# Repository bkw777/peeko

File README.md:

# PEEKO

Alternate PCB for [gusmanb/logicanalyzer](https://github.com/gusmanb/logicanalyzer)

[PEEKO.bom.csv](PCB/out/PEEKO.bom.csv)

# BOM

[DigiKey](https://www.digikey.com/short/h755hpzf)  ([PEEKO.bom.csv](PCB/out/PEEKO.bom.csv))

<!--
Alternate parts for chain:  
[header molex 2-pin male r/a](https://www.digikey.com/en/products/detail/molex/1718574002/5116867)  
[cable molex 2-pin female-female 150mm](https://www.digikey.com/en/products/detail/molex/2177961021/14637993)  
TODO:  
* Zigzag pico pin holes  
  so pico can be installed removable with only male pins soldered to the pico  
  this elevates the pico by the same amount as the molex pin headers over the plain pin headers (2.54mm)  
* Version of enclosure with 2.54mm taller walls  
* Lid to close up the enclosure, with opening for heat sink for overclocked pico2
* Printable legend for the input pins
-->

# PROBES

Cable: https://www.digikey.com/en/products/detail/digilent-inc/310-064/5848557

Mini-grabbers: [terrible](https://www.amazon.com/dp/B07BCZSNGS), [good](https://amazon.com/dp/B09TPBS7YF/147-7256223-7410705), [expensive](https://www.amazon.com/dp/B00R3R7IVC)

# FIRMWARE

Download *-PICO.uf2 from https://github.com/gusmanb/logicanalyzer/releases  
Hold BOOTSEL button while connecting usb.  
Drag *-PICO.uf2 onto the RPI-RP2 drive.

PICO will reboot itself immediately and RPI-RP2 drive will disappear. PEEKO is ready to use.

# USAGE

For software, firmware, & directions, see [gusmanb/logicanalyzer/wiki](https://github.com/gusmanb/logicanalyzer/wiki)

# Other Versions

Brute-force diode-clamping version: [brute-clamp](brute-clamp.md)

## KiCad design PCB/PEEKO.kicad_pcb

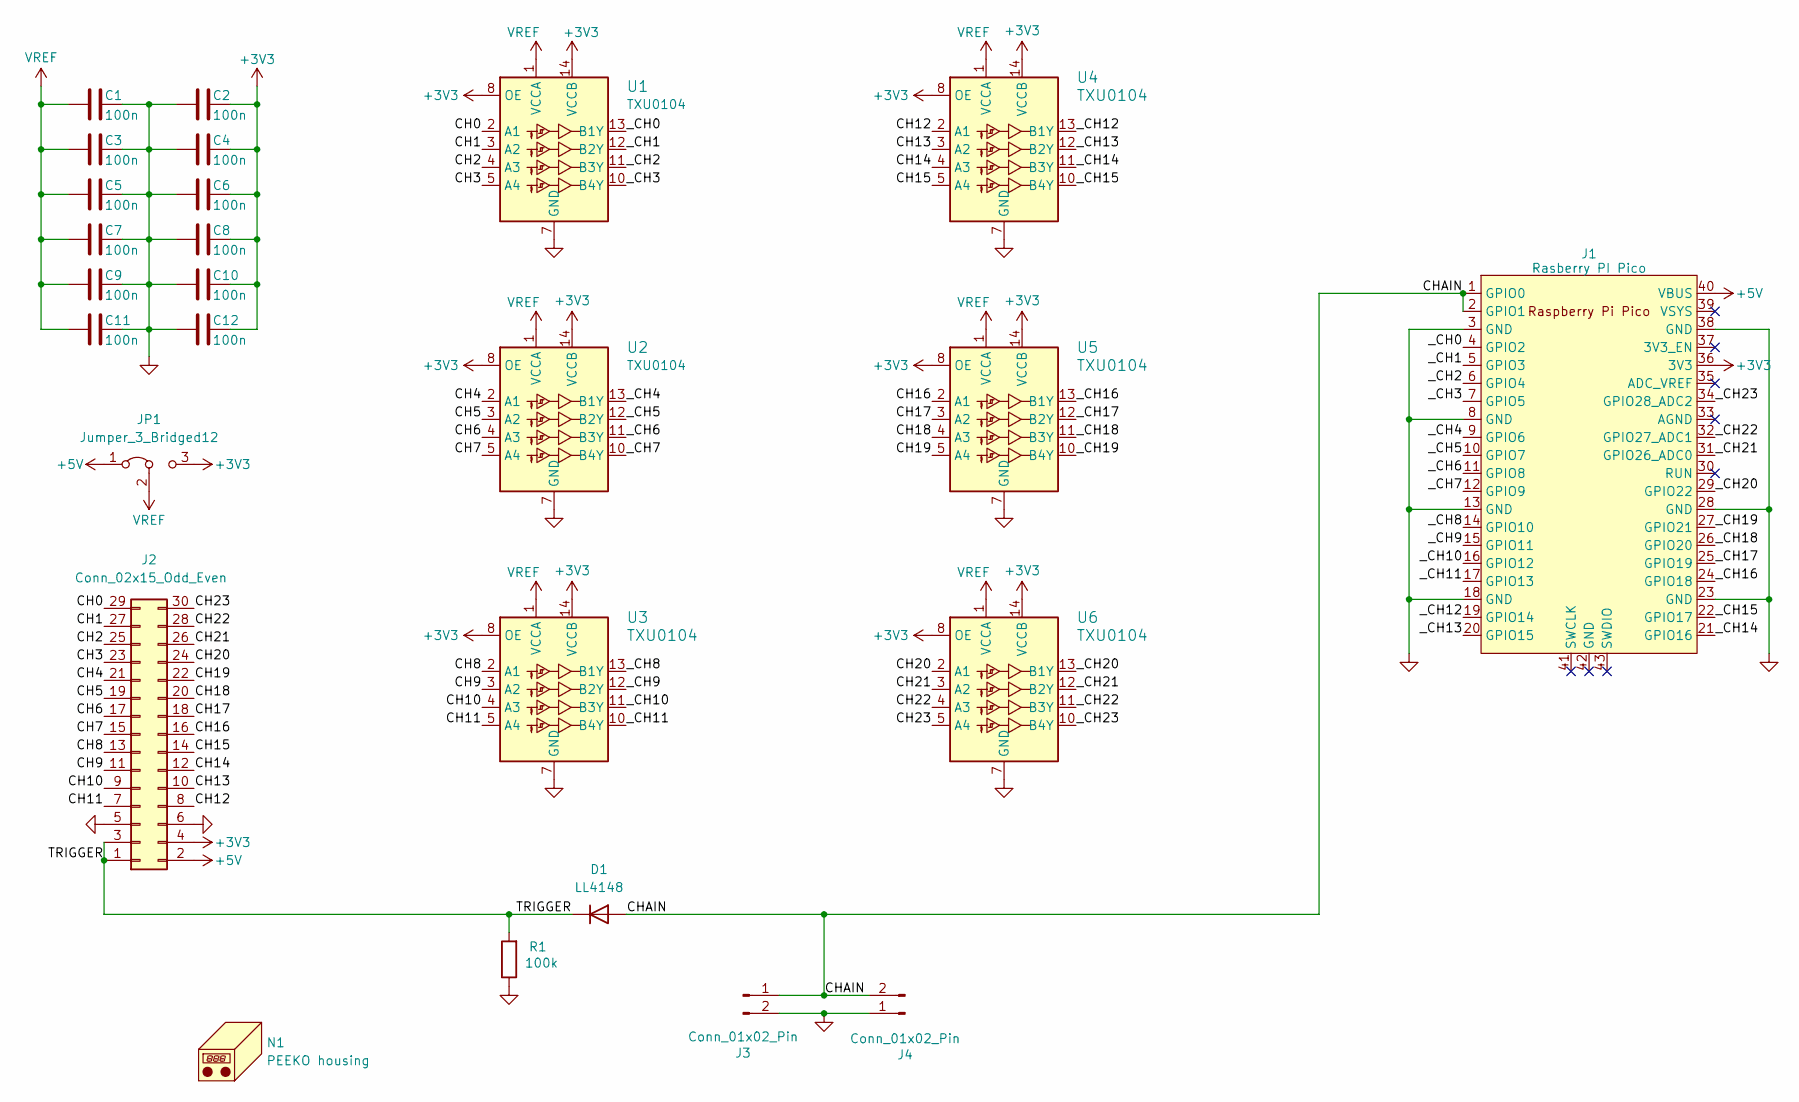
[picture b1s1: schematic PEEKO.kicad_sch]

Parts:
C1, C2, C3, C4, C5, C6, C7, C8, C9, C10, C11, C12: 100n; C_0805; MPN CC0805KRX7R9BB104
D1: LL4148; D_MiniMELF; MPN FDLL4148
J1: Rasberry PI Pico; dip-40-700-pi-pico-z; MPN SC0915
J2: Conn_02x15_Odd_Even; IDC_02x15_2.54_THT_male_pcb_edge; MPN SBH11-PBPC-D15-ST-BK
J3, J4: Conn_01x02_Pin; PinHeader_1x02_P2.54mm_Horizontal; MPN PH1RB-02-UA
JP1: Jumper_3_Bridged12; PinHeader_1x03_P2.54mm_Horizontal jumper 1-2; MPN PH1RB-03-UA
N1: PEEKO housing; PEEKO_housing
R1: 100k; R_0805; MPN RC0805FR-07100KL
U1, U2, U3, U4, U5, U6: TXU0104; TSSOP-14_4.4x5mm_P0.65mm; MPN TXU0104PW

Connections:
+3V3: C2.1, C4.1, C6.1, C8.1, C10.1, C12.1, J1.36 (3V3), J2.4, JP1.3 (B), U1.8 (OE), U1.14 (VCCB), U2.8 (OE), U2.14 (VCCB), U3.8 (OE), U3.14 (VCCB), U4.8 (OE), U4.14 (VCCB), U5.8 (OE), U5.14 (VCCB), U6.8 (OE), U6.14 (VCCB)
+5V: J1.40 (VBUS), J2.2, JP1.1 (A)
/CH0: J2.29, U1.2 (A1)
/CH1: J2.27, U1.3 (A2)
/CH2: J2.25, U1.4 (A3)
/CH3: J2.23, U1.5 (A4)
/CH4: J2.21, U2.2 (A1)
/CH5: J2.19, U2.3 (A2)
/CH6: J2.17, U2.4 (A3)
/CH7: J2.15, U2.5 (A4)
/CH8: J2.13, U3.2 (A1)
/CH9: J2.11, U3.3 (A2)
/CH10: J2.9, U3.4 (A3)
/CH11: J2.7, U3.5 (A4)
/CH12: J2.8, U4.2 (A1)
/CH13: J2.10, U4.3 (A2)
/CH14: J2.12, U4.4 (A3)
/CH15: J2.14, U4.5 (A4)
/CH16: J2.16, U5.2 (A1)
/CH17: J2.18, U5.3 (A2)
/CH18: J2.20, U5.4 (A3)
/CH19: J2.22, U5.5 (A4)
/CH20: J2.24, U6.2 (A1)
/CH21: J2.26, U6.3 (A2)
/CH22: J2.28, U6.4 (A3)
/CH23: J2.30, U6.5 (A4)
/CHAIN: D1.2 (A), J1.1 (GPIO0), J1.2 (GPIO1), J3.1, J4.2
/TRIGGER: D1.1 (K), J2.1, J2.3, R1.2
/_CH0: J1.4 (GPIO2), U1.13 (B1Y)
/_CH1: J1.5 (GPIO3), U1.12 (B2Y)
/_CH2: J1.6 (GPIO4), U1.11 (B3Y)
/_CH3: J1.7 (GPIO5), U1.10 (B4Y)
/_CH4: J1.9 (GPIO6), U2.13 (B1Y)
/_CH5: J1.10 (GPIO7), U2.12 (B2Y)
/_CH6: J1.11 (GPIO8), U2.11 (B3Y)
/_CH7: J1.12 (GPIO9), U2.10 (B4Y)
/_CH8: J1.14 (GPIO10), U3.13 (B1Y)
/_CH9: J1.15 (GPIO11), U3.12 (B2Y)
/_CH10: J1.16 (GPIO12), U3.11 (B3Y)
/_CH11: J1.17 (GPIO13), U3.10 (B4Y)
/_CH12: J1.19 (GPIO14), U4.13 (B1Y)
/_CH13: J1.20 (GPIO15), U4.12 (B2Y)
/_CH14: J1.21 (GPIO16), U4.11 (B3Y)
/_CH15: J1.22 (GPIO17), U4.10 (B4Y)
/_CH16: J1.24 (GPIO18), U5.13 (B1Y)
/_CH17: J1.25 (GPIO19), U5.12 (B2Y)
/_CH18: J1.26 (GPIO20), U5.11 (B3Y)
/_CH19: J1.27 (GPIO21), U5.10 (B4Y)
/_CH20: J1.29 (GPIO22), U6.13 (B1Y)
/_CH21: J1.31 (GPIO26_ADC0), U6.12 (B2Y)
/_CH22: J1.32 (GPIO27_ADC1), U6.11 (B3Y)
/_CH23: J1.34 (GPIO28_ADC2), U6.10 (B4Y)
GND: C1.1, C2.2, C3.1, C4.2, C5.1, C6.2, C7.1, C8.2, C9.1, C10.2, C11.1, C12.2, J1.3 (GND), J1.8 (GND), J1.13 (GND), J1.18 (GND), J1.23 (GND), J1.28 (GND), J1.38 (GND), J2.5, J2.6, J3.2, J4.1, R1.1, U1.7 (GND), U2.7 (GND), U3.7 (GND), U4.7 (GND), U5.7 (GND), U6.7 (GND)
VREF: C1.2, C3.2, C5.2, C7.2, C9.2, C11.2, JP1.2 (C), U1.1 (VCCA), U2.1 (VCCA), U3.1 (VCCA), U4.1 (VCCA), U5.1 (VCCA), U6.1 (VCCA)

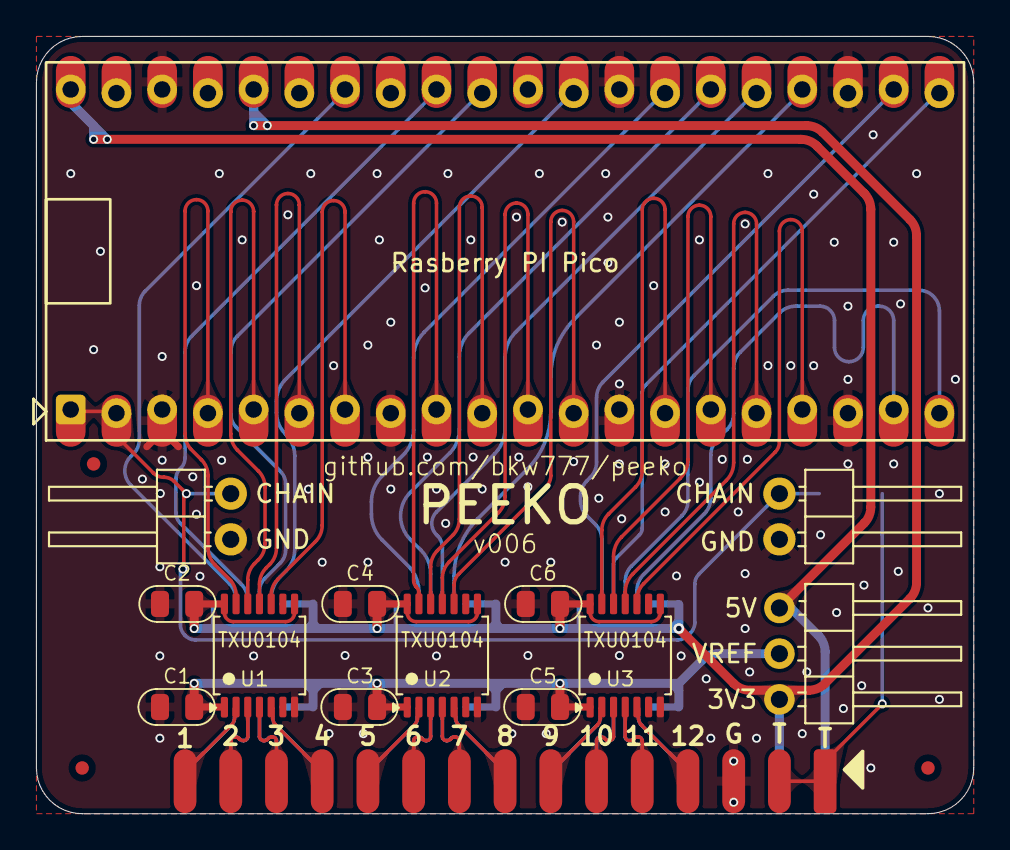
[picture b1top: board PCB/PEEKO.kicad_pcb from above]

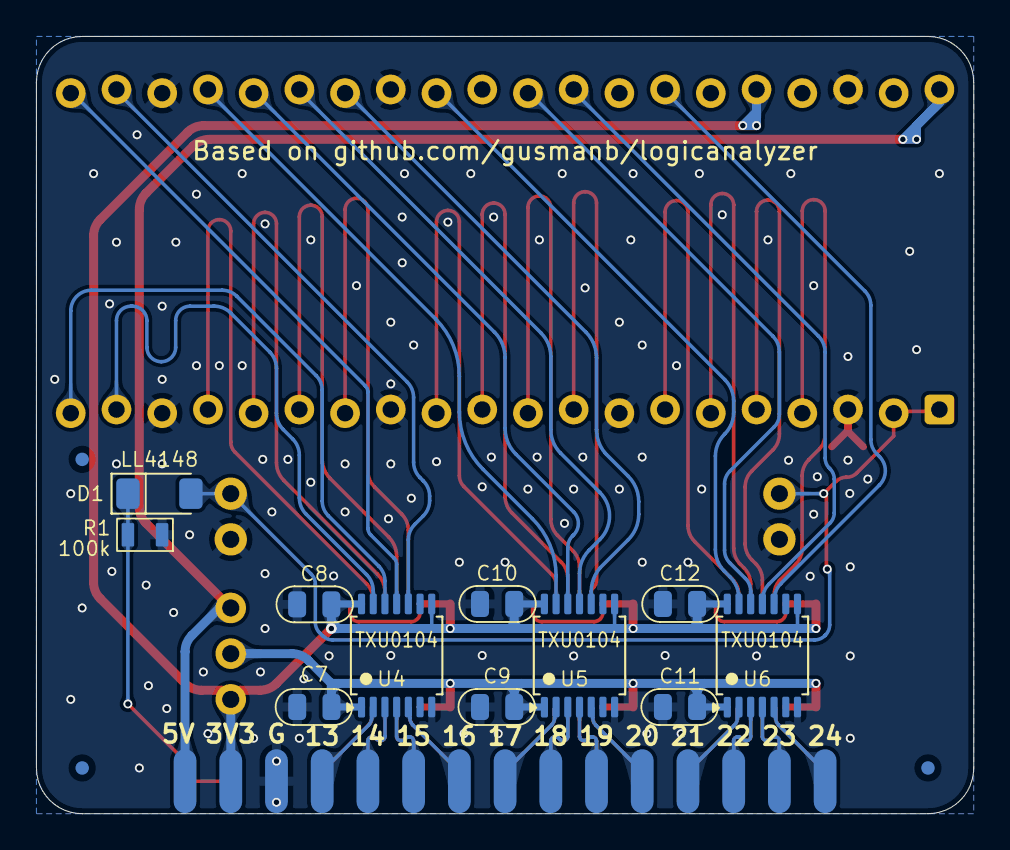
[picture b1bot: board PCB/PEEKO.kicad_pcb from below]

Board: 2 copper layers, 52.1 x 43.2 mm, 26 parts (11 on the bottom side), 54 nets.

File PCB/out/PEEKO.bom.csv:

"Reference","Value","Datasheet","Footprint","Qty","DNP","MPN","Description"
"C1,C2,C3,C4,C5,C6,C7,C8,C9,C10,C11,C12","100n","datasheets/UPY-GPHC_X7R_6.3V-to-250V_24.pdf","000_LOCAL:C_0805","12","","CC0805KRX7R9BB104","CAP CER 0.1UF 50V X7R 0805"
"D1","LL4148","datasheets/ll4148.pdf","000_LOCAL:D_MiniMELF","1","","FDLL4148","50V 1A General Purpose Rectifier Diode"
"J1","Rasberry PI Pico","datasheets/rpi-pico.pdf","000_LOCAL:dip-40-700-pi-pico","1","","SC0915","RASPBERRY PI PICO RP2040"
"J2","Conn_02x15_Odd_Even","datasheets/SBH11.pdf","000_LOCAL:IDC_02x15_2.54_THT_male_pcb_edge","1","","SBH11-PBPC-D15-ST-BK","CONN HEADER VERT 30POS 2.54MM"
"J3,J4","Conn_01x02_Pin","~","000_LOCAL:PinHeader_1x02_P2.54mm_Horizontal","2","","PH1RB-02-UA","CONN HEADER R/A 2POS 2.54MM"
"R1","100k","datasheets/PYu-RC_Group_51_RoHS_L_12.pdf","000_LOCAL:R_0805","1","","RC0805FR-07100KL","RES 100K OHM 1% 1/8W 0805"
"U1,U2,U3,U4,U5,U6","TXU0104","datasheets/txu0104.pdf","000_LOCAL:TSSOP-14_4.4x5mm_P0.65mm","6","","TXU0104PW","4-Bit Unidirectional Voltage-Level Translator, Schmitt trigger input, tri-state output, 1.1v to 5.5v, vTSSOP-14"

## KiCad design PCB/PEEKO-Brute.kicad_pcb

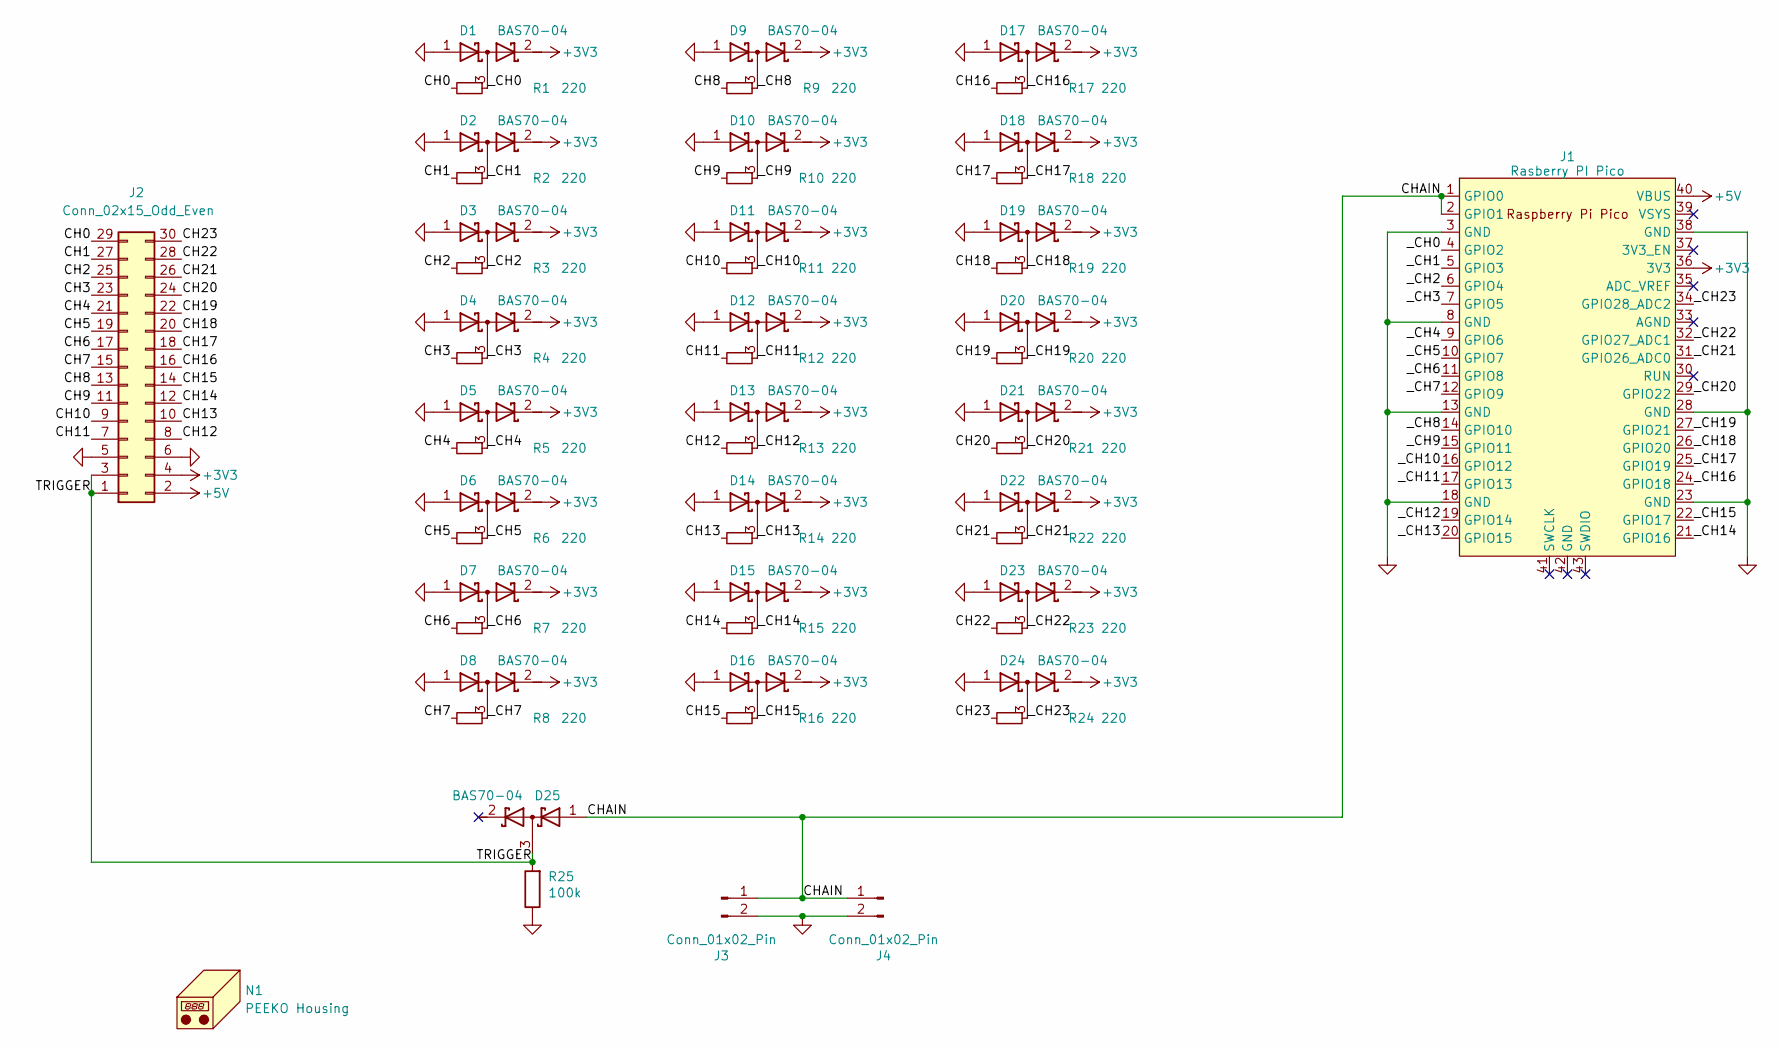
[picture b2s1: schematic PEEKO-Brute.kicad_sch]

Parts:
D1, D2, D3, D4, D5, D6, D7, D8, D9, D10, D11, D12, D13, D14, D15, D16, D17, D18, D19, D20, D21, D22, D23, D24, D25: BAS70-04; SC-59
J1: Rasberry PI Pico; dip-40-700-pi-pico; MPN SC0915
J2: Conn_02x15_Odd_Even; IDC_02x15_2.54_THT_male_pcb_edge; MPN SBH11-PBPC-D15-ST-BK
J3, J4: Conn_01x02_Pin; PinHeader_1x02_P2.54mm_Horizontal; MPN PH1RB-02-UA
N1: PEEKO Housing; PEEKO_housing
R1, R2, R3, R4, R5, R6, R7, R8, R9, R10, R11, R12, R13, R14, R15, R16, R17, R18, R19, R20, R21, R22, R23, R24: 220; R_0805; MPN CRGCQ0805F220R
R25: 100k; R_0805; MPN RC0805FR-07100KL

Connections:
+3V3: D1.2 (K), D2.2 (K), D3.2 (K), D4.2 (K), D5.2 (K), D6.2 (K), D7.2 (K), D8.2 (K), D9.2 (K), D10.2 (K), D11.2 (K), D12.2 (K), D13.2 (K), D14.2 (K), D15.2 (K), D16.2 (K), D17.2 (K), D18.2 (K), D19.2 (K), D20.2 (K), D21.2 (K), D22.2 (K), D23.2 (K), D24.2 (K), J1.36 (3V3), J2.4
+5V: J1.40 (VBUS), J2.2
/CH0: J2.29, R1.2
/CH1: J2.27, R2.2
/CH2: J2.25, R3.2
/CH3: J2.23, R4.2
/CH4: J2.21, R5.2
/CH5: J2.19, R6.2
/CH6: J2.17, R7.2
/CH7: J2.15, R8.2
/CH8: J2.13, R9.2
/CH9: J2.11, R10.2
/CH10: J2.9, R11.2
/CH11: J2.7, R12.2
/CH12: J2.8, R13.2
/CH13: J2.10, R14.2
/CH14: J2.12, R15.2
/CH15: J2.14, R16.2
/CH16: J2.16, R17.2
/CH17: J2.18, R18.2
/CH18: J2.20, R19.2
/CH19: J2.22, R20.2
/CH20: J2.24, R21.2
/CH21: J2.26, R22.2
/CH22: J2.28, R23.2
/CH23: J2.30, R24.2
/CHAIN: D25.1 (A), J1.1 (GPIO0), J1.2 (GPIO1), J3.1, J4.1
/TRIGGER: D25.3 (common), J2.1, J2.3, R25.2
/_CH0: D1.3 (common), J1.4 (GPIO2), R1.1
/_CH1: D2.3 (common), J1.5 (GPIO3), R2.1
/_CH2: D3.3 (common), J1.6 (GPIO4), R3.1
/_CH3: D4.3 (common), J1.7 (GPIO5), R4.1
/_CH4: D5.3 (common), J1.9 (GPIO6), R5.1
/_CH5: D6.3 (common), J1.10 (GPIO7), R6.1
/_CH6: D7.3 (common), J1.11 (GPIO8), R7.1
/_CH7: D8.3 (common), J1.12 (GPIO9), R8.1
/_CH8: D9.3 (common), J1.14 (GPIO10), R9.1
/_CH9: D10.3 (common), J1.15 (GPIO11), R10.1
/_CH10: D11.3 (common), J1.16 (GPIO12), R11.1
/_CH11: D12.3 (common), J1.17 (GPIO13), R12.1
/_CH12: D13.3 (common), J1.19 (GPIO14), R13.1
/_CH13: D14.3 (common), J1.20 (GPIO15), R14.1
/_CH14: D15.3 (common), J1.21 (GPIO16), R15.1
/_CH15: D16.3 (common), J1.22 (GPIO17), R16.1
/_CH16: D17.3 (common), J1.24 (GPIO18), R17.1
/_CH17: D18.3 (common), J1.25 (GPIO19), R18.1
/_CH18: D19.3 (common), J1.26 (GPIO20), R19.1
/_CH19: D20.3 (common), J1.27 (GPIO21), R20.1
/_CH20: D21.3 (common), J1.29 (GPIO22), R21.1
/_CH21: D22.3 (common), J1.31 (GPIO26_ADC0), R22.1
/_CH22: D23.3 (common), J1.32 (GPIO27_ADC1), R23.1
/_CH23: D24.3 (common), J1.34 (GPIO28_ADC2), R24.1
GND: D1.1 (A), D2.1 (A), D3.1 (A), D4.1 (A), D5.1 (A), D6.1 (A), D7.1 (A), D8.1 (A), D9.1 (A), D10.1 (A), D11.1 (A), D12.1 (A), D13.1 (A), D14.1 (A), D15.1 (A), D16.1 (A), D17.1 (A), D18.1 (A), D19.1 (A), D20.1 (A), D21.1 (A), D22.1 (A), D23.1 (A), D24.1 (A), J1.3 (GND), J1.8 (GND), J1.13 (GND), J1.18 (GND), J1.23 (GND), J1.28 (GND), J1.38 (GND), J2.5, J2.6, J3.2, J4.2, R25.1

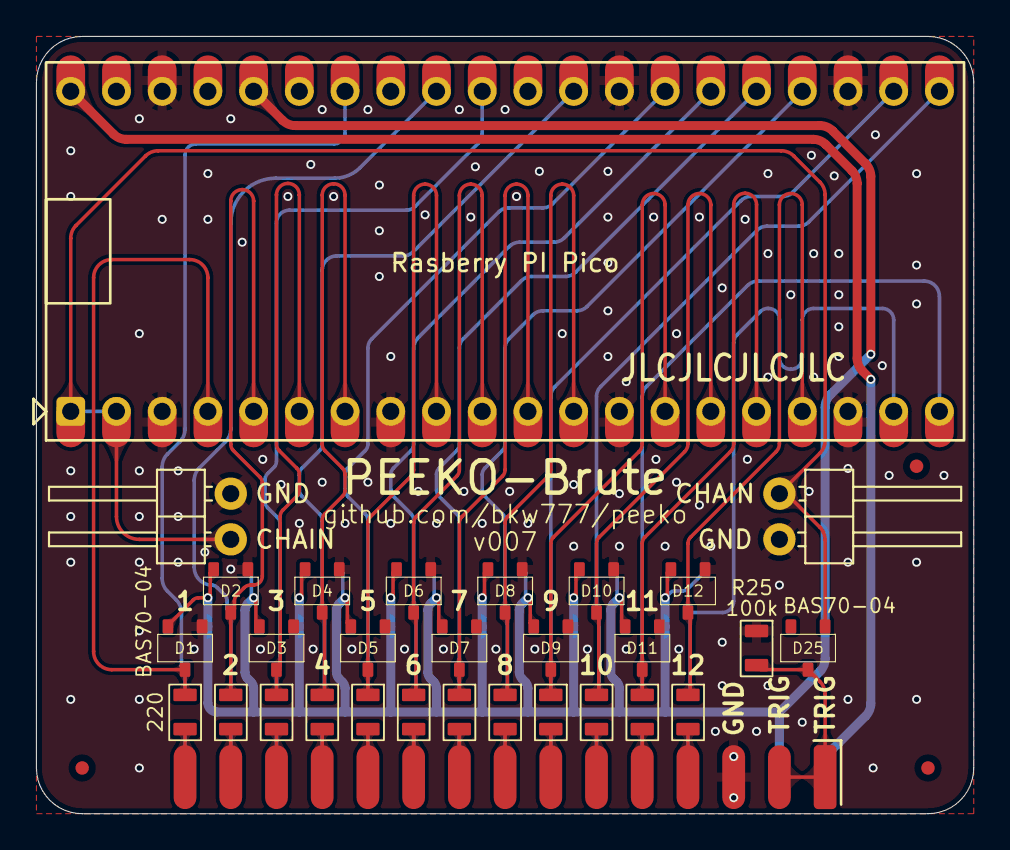
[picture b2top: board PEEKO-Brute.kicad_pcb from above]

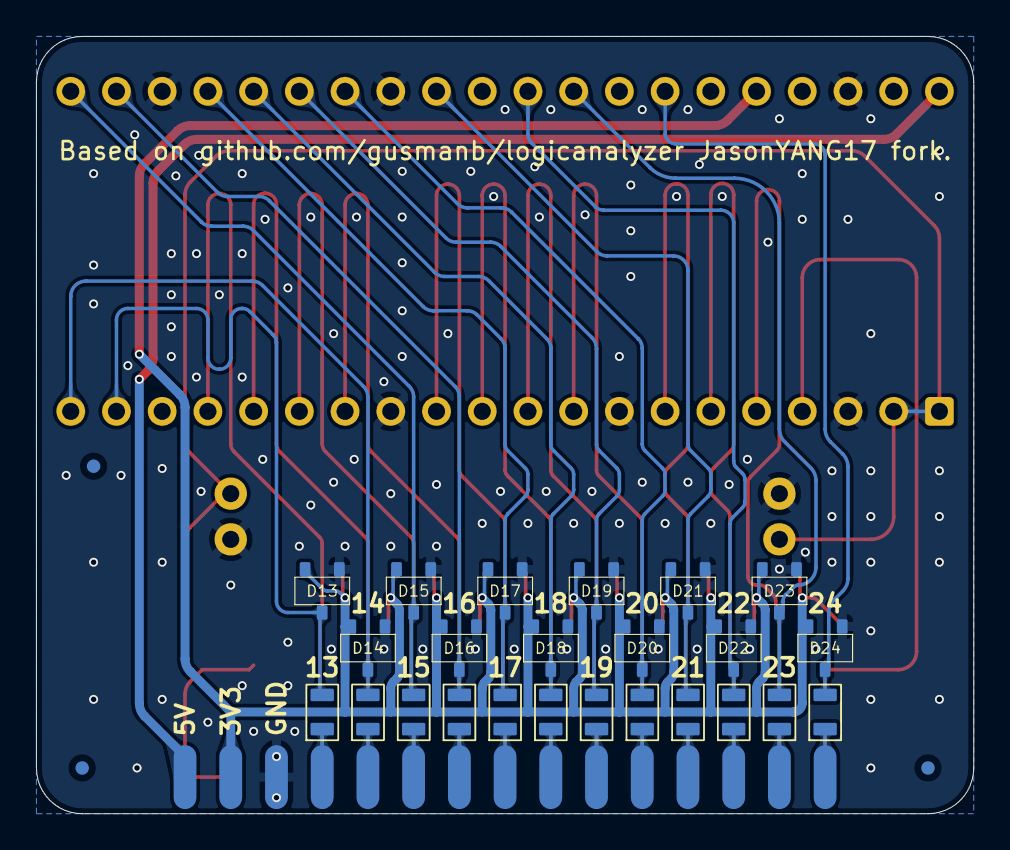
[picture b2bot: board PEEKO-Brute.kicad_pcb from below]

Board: 2 copper layers, 52.1 x 43.2 mm, 55 parts (24 on the bottom side), 53 nets.

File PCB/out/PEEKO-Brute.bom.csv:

"Reference","Value","Datasheet","Footprint","Qty","DNP","MPN"
"D1,D2,D3,D4,D5,D6,D7,D8,D9,D10,D11,D12,D13,D14,D15,D16,D17,D18,D19,D20,D21,D22,D23,D24,D25","BAS70-04","datasheets/INFNS30154-1.pdf","000_LOCAL:SC-59","25","","BAS70-04"
"J1","Rasberry PI Pico","datasheets/rpi-pico.pdf","000_LOCAL:dip-40-700-pi-pico","1","","SC0915"
"J2","Conn_02x15_Odd_Even","datasheets/SBH11.pdf","000_LOCAL:IDC_02x15_2.54_THT_male_pcb_edge","1","","SBH11-PBPC-D15-ST-BK"
"J3,J4","Conn_01x02_Pin","~","000_LOCAL:PinHeader_1x02_P2.54mm_Horizontal","2","","PH1RB-02-UA"
"R1,R2,R3,R4,R5,R6,R7,R8,R9,R10,R11,R12,R13,R14,R15,R16,R17,R18,R19,R20,R21,R22,R23,R24","220","datasheets/TE-1-2176341-7.pdf","000_LOCAL:R_0805","24","","CRGCQ0805F220R"
"R25","100k","datasheets/PYu-RC_Group_51_RoHS_L_12.pdf","000_LOCAL:R_0805","1","","RC0805FR-07100KL"

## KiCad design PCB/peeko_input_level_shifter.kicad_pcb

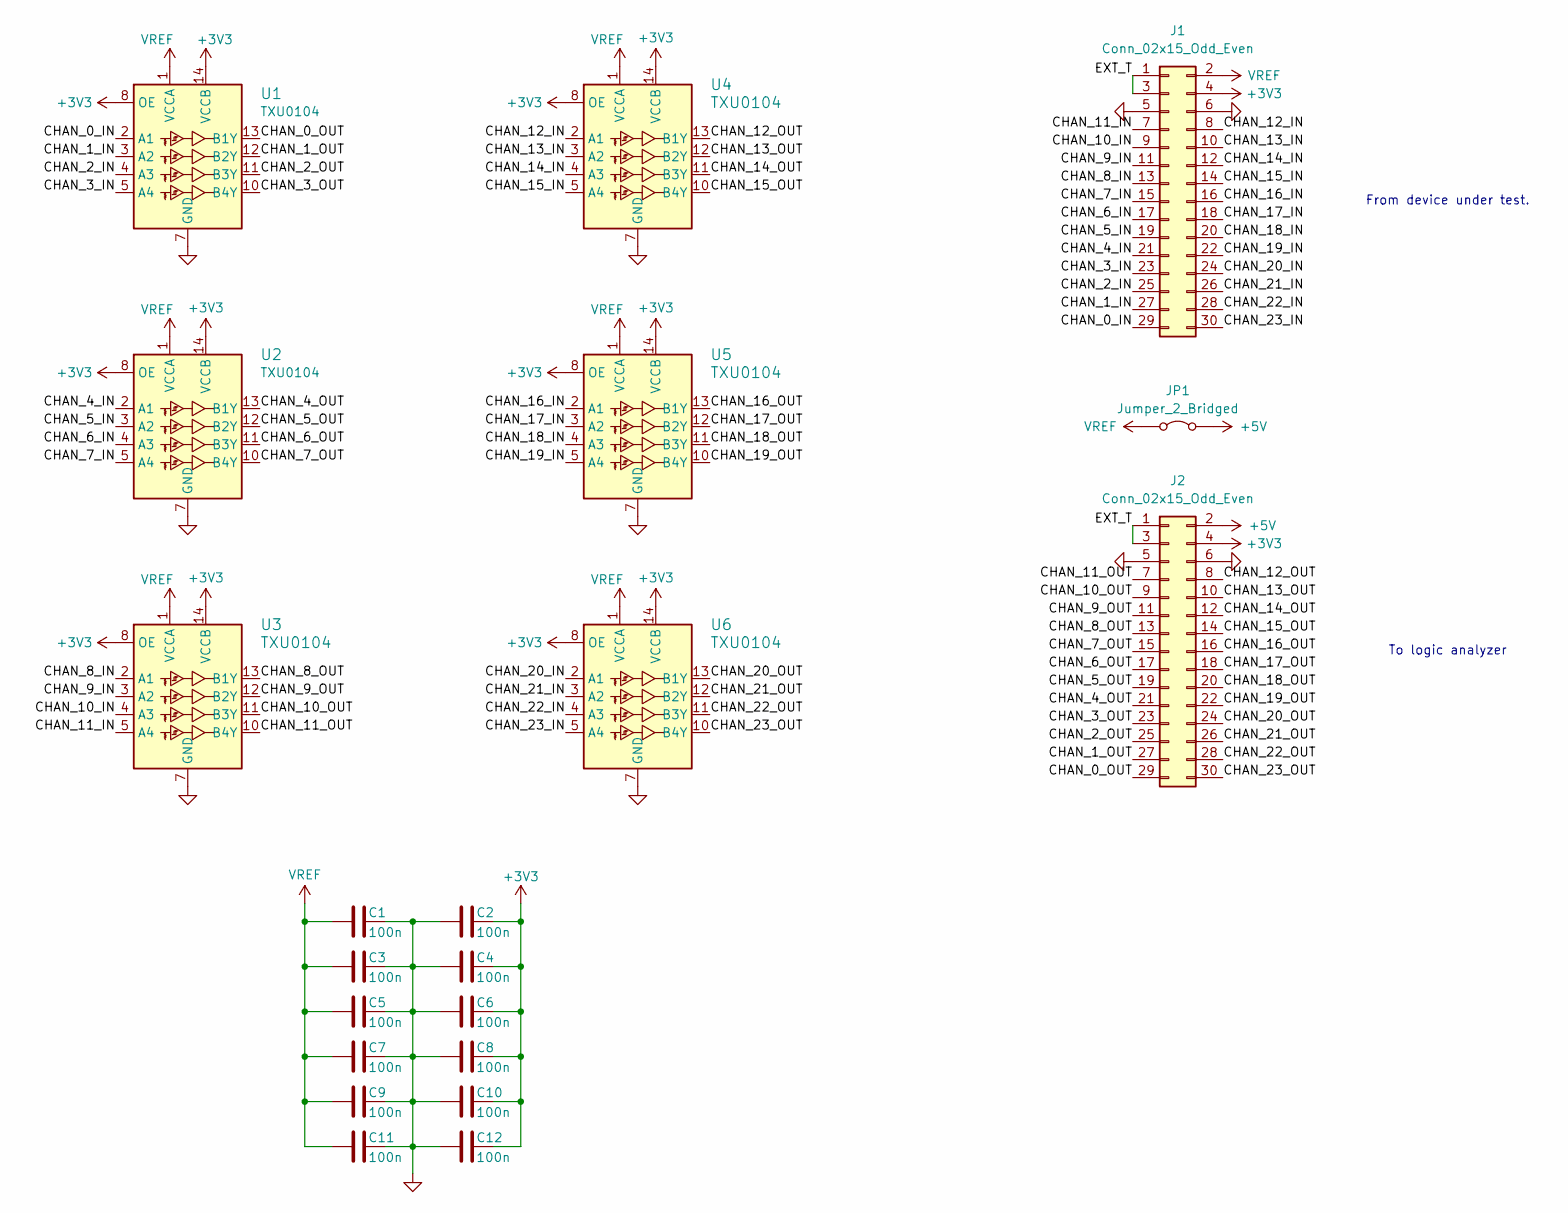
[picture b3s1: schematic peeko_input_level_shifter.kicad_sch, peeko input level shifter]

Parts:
C1, C2, C3, C4, C5, C6, C7, C8, C9, C10, C11, C12: 100n; C_0805
J1: Conn_02x15_Odd_Even; IDC_02x15_2.54_THT_male_pcb_edge
J2: Conn_02x15_Odd_Even; IDC_02x15_2.54_THT_female_pcb_edge
JP1: Jumper_2_Bridged; PinHeader_1x02_P2.54mm_Horizontal jumper closed
U1, U2, U3, U4, U5, U6: TXU0104; TSSOP-14_4.4x5mm_P0.65mm

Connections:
+3V3: C2.1, C4.1, C6.1, C8.1, C10.1, C12.1, J1.4, J2.4, U1.8 (OE), U1.14 (VCCB), U2.8 (OE), U2.14 (VCCB), U3.8 (OE), U3.14 (VCCB), U4.8 (OE), U4.14 (VCCB), U5.8 (OE), U5.14 (VCCB), U6.8 (OE), U6.14 (VCCB)
+5V: J2.2, JP1.1 (A)
/CHAN_0_IN: J1.29, U1.2 (A1)
/CHAN_0_OUT: J2.29, U1.13 (B1Y)
/CHAN_1_IN: J1.27, U1.3 (A2)
/CHAN_1_OUT: J2.27, U1.12 (B2Y)
/CHAN_2_IN: J1.25, U1.4 (A3)
/CHAN_2_OUT: J2.25, U1.11 (B3Y)
/CHAN_3_IN: J1.23, U1.5 (A4)
/CHAN_3_OUT: J2.23, U1.10 (B4Y)
/CHAN_4_IN: J1.21, U2.2 (A1)
/CHAN_4_OUT: J2.21, U2.13 (B1Y)
/CHAN_5_IN: J1.19, U2.3 (A2)
/CHAN_5_OUT: J2.19, U2.12 (B2Y)
/CHAN_6_IN: J1.17, U2.4 (A3)
/CHAN_6_OUT: J2.17, U2.11 (B3Y)
/CHAN_7_IN: J1.15, U2.5 (A4)
/CHAN_7_OUT: J2.15, U2.10 (B4Y)
/CHAN_8_IN: J1.13, U3.2 (A1)
/CHAN_8_OUT: J2.13, U3.13 (B1Y)
/CHAN_9_IN: J1.11, U3.3 (A2)
/CHAN_9_OUT: J2.11, U3.12 (B2Y)
/CHAN_10_IN: J1.9, U3.4 (A3)
/CHAN_10_OUT: J2.9, U3.11 (B3Y)
/CHAN_11_IN: J1.7, U3.5 (A4)
/CHAN_11_OUT: J2.7, U3.10 (B4Y)
/CHAN_12_IN: J1.8, U4.2 (A1)
/CHAN_12_OUT: J2.8, U4.13 (B1Y)
/CHAN_13_IN: J1.10, U4.3 (A2)
/CHAN_13_OUT: J2.10, U4.12 (B2Y)
/CHAN_14_IN: J1.12, U4.4 (A3)
/CHAN_14_OUT: J2.12, U4.11 (B3Y)
/CHAN_15_IN: J1.14, U4.5 (A4)
/CHAN_15_OUT: J2.14, U4.10 (B4Y)
/CHAN_16_IN: J1.16, U5.2 (A1)
/CHAN_16_OUT: J2.16, U5.13 (B1Y)
/CHAN_17_IN: J1.18, U5.3 (A2)
/CHAN_17_OUT: J2.18, U5.12 (B2Y)
/CHAN_18_IN: J1.20, U5.4 (A3)
/CHAN_18_OUT: J2.20, U5.11 (B3Y)
/CHAN_19_IN: J1.22, U5.5 (A4)
/CHAN_19_OUT: J2.22, U5.10 (B4Y)
/CHAN_20_IN: J1.24, U6.2 (A1)
/CHAN_20_OUT: J2.24, U6.13 (B1Y)
/CHAN_21_IN: J1.26, U6.3 (A2)
/CHAN_21_OUT: J2.26, U6.12 (B2Y)
/CHAN_22_IN: J1.28, U6.4 (A3)
/CHAN_22_OUT: J2.28, U6.11 (B3Y)
/CHAN_23_IN: J1.30, U6.5 (A4)
/CHAN_23_OUT: J2.30, U6.10 (B4Y)
/EXT_T: J1.1, J1.3, J2.1, J2.3
GND: C1.1, C2.2, C3.1, C4.2, C5.1, C6.2, C7.1, C8.2, C9.1, C10.2, C11.1, C12.2, J1.5, J1.6, J2.5, J2.6, U1.7 (GND), U2.7 (GND), U3.7 (GND), U4.7 (GND), U5.7 (GND), U6.7 (GND)
VREF: C1.2, C3.2, C5.2, C7.2, C9.2, C11.2, J1.2, JP1.2 (B), U1.1 (VCCA), U2.1 (VCCA), U3.1 (VCCA), U4.1 (VCCA), U5.1 (VCCA), U6.1 (VCCA)

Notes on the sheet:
To logic analyzer
From device under test.

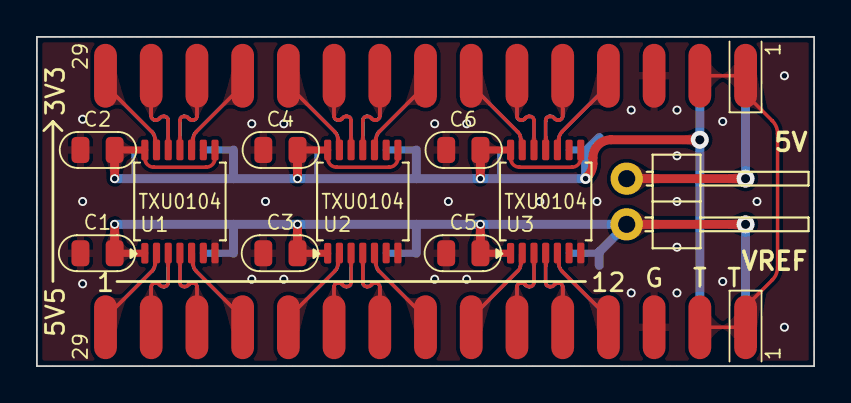
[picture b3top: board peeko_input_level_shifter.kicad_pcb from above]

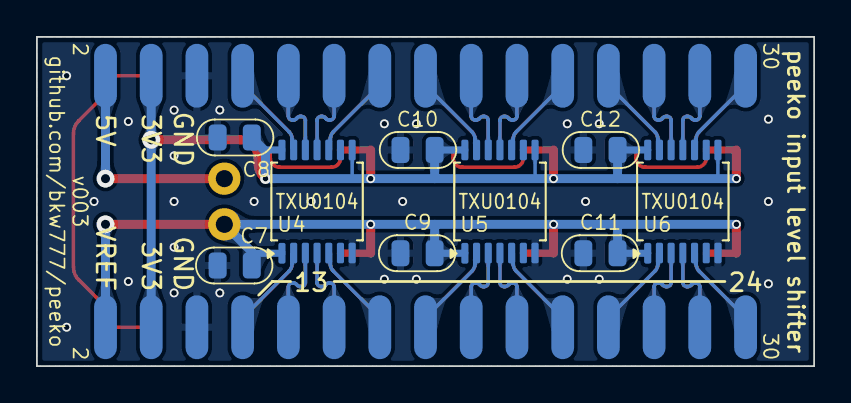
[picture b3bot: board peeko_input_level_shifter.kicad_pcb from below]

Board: 2 copper layers, 43.2 x 18.3 mm, 21 parts (9 on the bottom side), 53 nets.

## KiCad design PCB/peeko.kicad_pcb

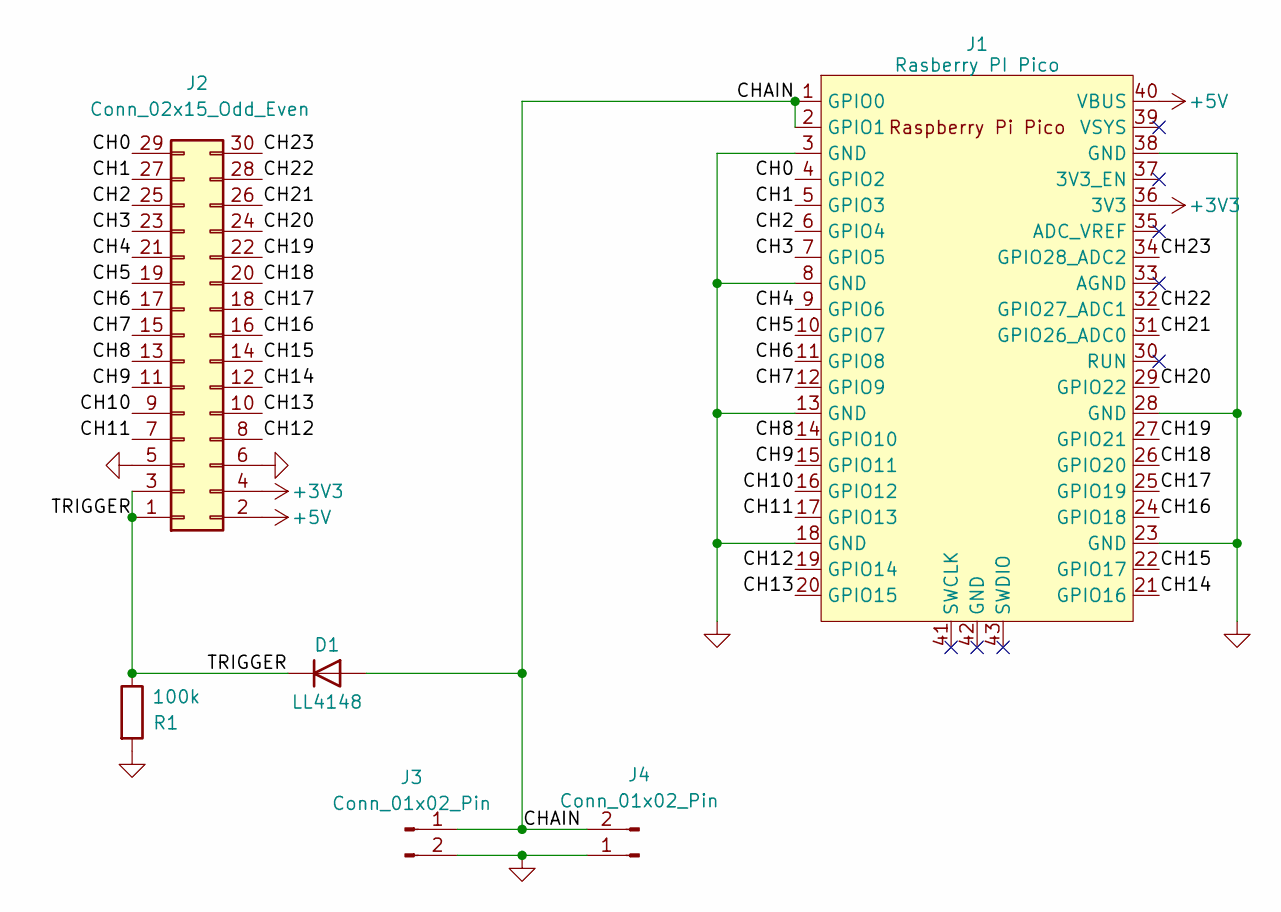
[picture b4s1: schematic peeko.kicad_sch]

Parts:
D1: LL4148; D_MiniMELF
J1: Rasberry PI Pico; DIP_40_700
J2: Conn_02x15_Odd_Even; IDC-Header_2x15_P2.54mm_Horizontal
J3, J4: Conn_01x02_Pin; PinHeader_1x02_P2.54mm_Horizontal
R1: 100k; R_0805

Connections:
+3V3: J1.36 (3V3), J2.4
+5V: J1.40 (VBUS), J2.2
/CH0: J1.4 (GPIO2), J2.29
/CH1: J1.5 (GPIO3), J2.27
/CH2: J1.6 (GPIO4), J2.25
/CH3: J1.7 (GPIO5), J2.23
/CH4: J1.9 (GPIO6), J2.21
/CH5: J1.10 (GPIO7), J2.19
/CH6: J1.11 (GPIO8), J2.17
/CH7: J1.12 (GPIO9), J2.15
/CH8: J1.14 (GPIO10), J2.13
/CH9: J1.15 (GPIO11), J2.11
/CH10: J1.16 (GPIO12), J2.9
/CH11: J1.17 (GPIO13), J2.7
/CH12: J1.19 (GPIO14), J2.8
/CH13: J1.20 (GPIO15), J2.10
/CH14: J1.21 (GPIO16), J2.12
/CH15: J1.22 (GPIO17), J2.14
/CH16: J1.24 (GPIO18), J2.16
/CH17: J1.25 (GPIO19), J2.18
/CH18: J1.26 (GPIO20), J2.20
/CH19: J1.27 (GPIO21), J2.22
/CH20: J1.29 (GPIO22), J2.24
/CH21: J1.31 (GPIO26_ADC0), J2.26
/CH22: J1.32 (GPIO27_ADC1), J2.28
/CH23: J1.34 (GPIO28_ADC2), J2.30
/CHAIN: D1.2 (A), J1.1 (GPIO0), J1.2 (GPIO1), J3.1, J4.2
/TRIGGER: D1.1 (K), J2.1, J2.3, R1.1
GND: J1.3 (GND), J1.8 (GND), J1.13 (GND), J1.18 (GND), J1.23 (GND), J1.28 (GND), J1.38 (GND), J2.5, J2.6, J3.2, J4.1, R1.2

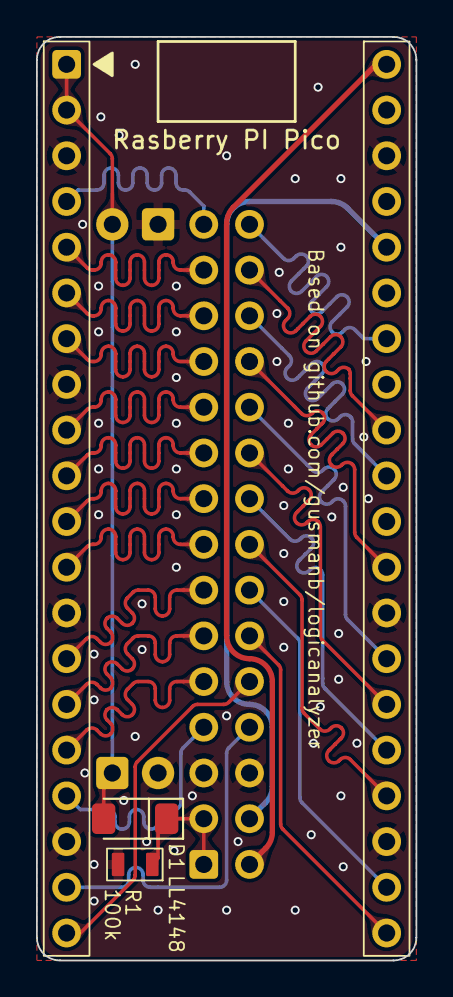
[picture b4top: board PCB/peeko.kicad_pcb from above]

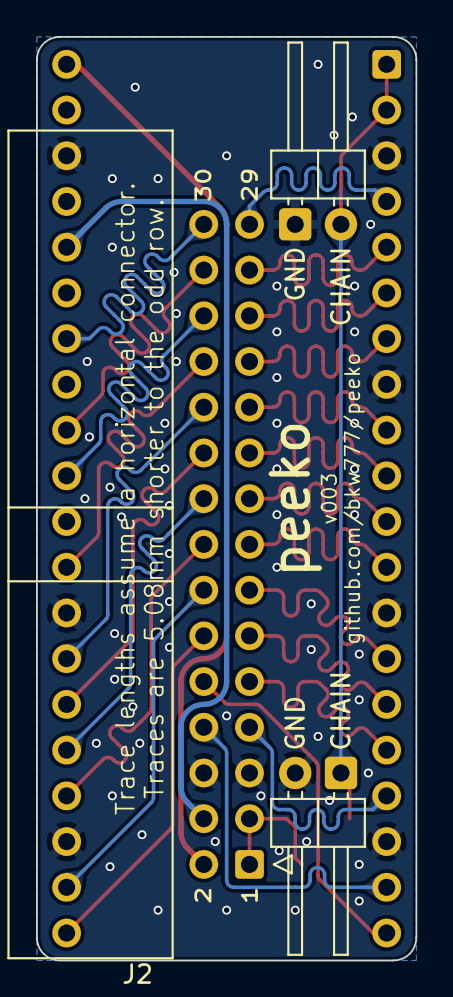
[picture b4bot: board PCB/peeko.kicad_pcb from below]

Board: 2 copper layers, 21.1 x 51.3 mm, 6 parts (3 on the bottom side), 29 nets.

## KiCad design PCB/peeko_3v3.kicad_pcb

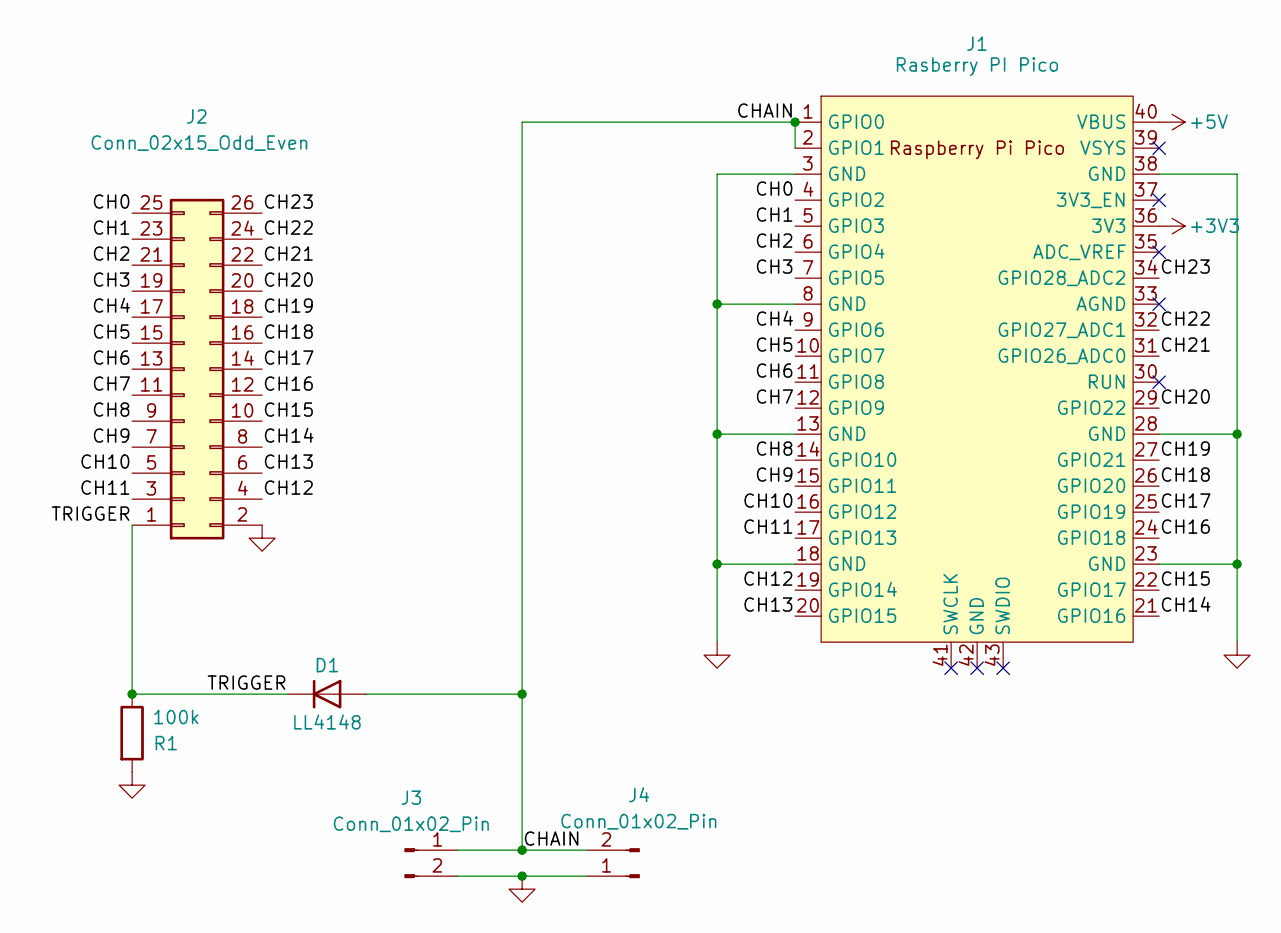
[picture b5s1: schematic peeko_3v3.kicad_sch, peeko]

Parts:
D1: LL4148; D_MiniMELF
J1: Rasberry PI Pico; DIP_40_700
J2: Conn_02x15_Odd_Even; IDC-Header_2x13_P2.54mm_Horizontal
J3, J4: Conn_01x02_Pin; PinHeader_1x02_P2.54mm_Horizontal
R1: 100k; R_0805

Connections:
+3V3: J1.36 (3V3)
+5V: J1.40 (VBUS)
/CH0: J1.4 (GPIO2), J2.25
/CH1: J1.5 (GPIO3), J2.23
/CH2: J1.6 (GPIO4), J2.21
/CH3: J1.7 (GPIO5), J2.19
/CH4: J1.9 (GPIO6), J2.17
/CH5: J1.10 (GPIO7), J2.15
/CH6: J1.11 (GPIO8), J2.13
/CH7: J1.12 (GPIO9), J2.11
/CH8: J1.14 (GPIO10), J2.9
/CH9: J1.15 (GPIO11), J2.7
/CH10: J1.16 (GPIO12), J2.5
/CH11: J1.17 (GPIO13), J2.3
/CH12: J1.19 (GPIO14), J2.4
/CH13: J1.20 (GPIO15), J2.6
/CH14: J1.21 (GPIO16), J2.8
/CH15: J1.22 (GPIO17), J2.10
/CH16: J1.24 (GPIO18), J2.12
/CH17: J1.25 (GPIO19), J2.14
/CH18: J1.26 (GPIO20), J2.16
/CH19: J1.27 (GPIO21), J2.18
/CH20: J1.29 (GPIO22), J2.20
/CH21: J1.31 (GPIO26_ADC0), J2.22
/CH22: J1.32 (GPIO27_ADC1), J2.24
/CH23: J1.34 (GPIO28_ADC2), J2.26
/CHAIN: D1.2 (A), J1.1 (GPIO0), J1.2 (GPIO1), J3.1, J4.2
/TRIGGER: D1.1 (K), J2.1, R1.1
GND: J1.3 (GND), J1.8 (GND), J1.13 (GND), J1.18 (GND), J1.23 (GND), J1.28 (GND), J1.38 (GND), J2.2, J3.2, J4.1, R1.2

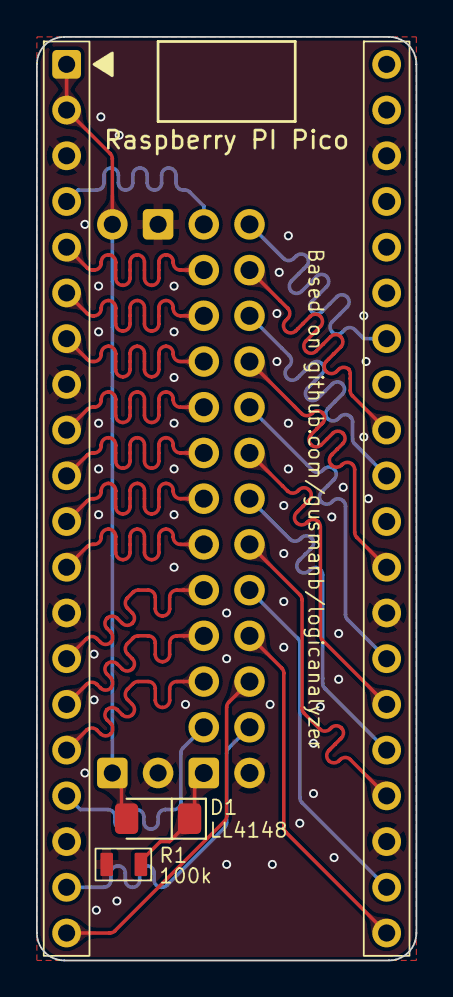
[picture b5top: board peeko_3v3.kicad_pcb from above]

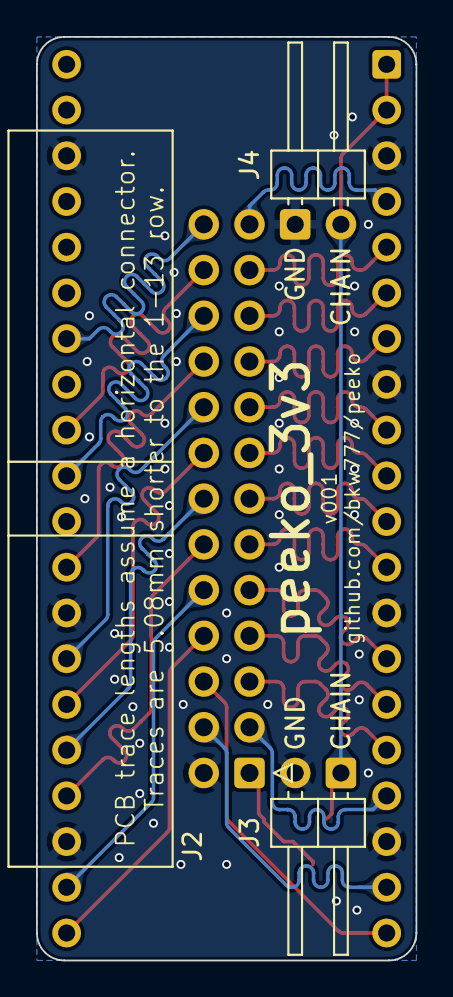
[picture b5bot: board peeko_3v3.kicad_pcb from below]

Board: 2 copper layers, 21.1 x 51.3 mm, 6 parts (3 on the bottom side), 27 nets.

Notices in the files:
PCB/LevelShifter.kicad_pcb:
(c)2022
parts and their libraries:
Copyright 2021 Accelerated Designs. All rights reserved.
